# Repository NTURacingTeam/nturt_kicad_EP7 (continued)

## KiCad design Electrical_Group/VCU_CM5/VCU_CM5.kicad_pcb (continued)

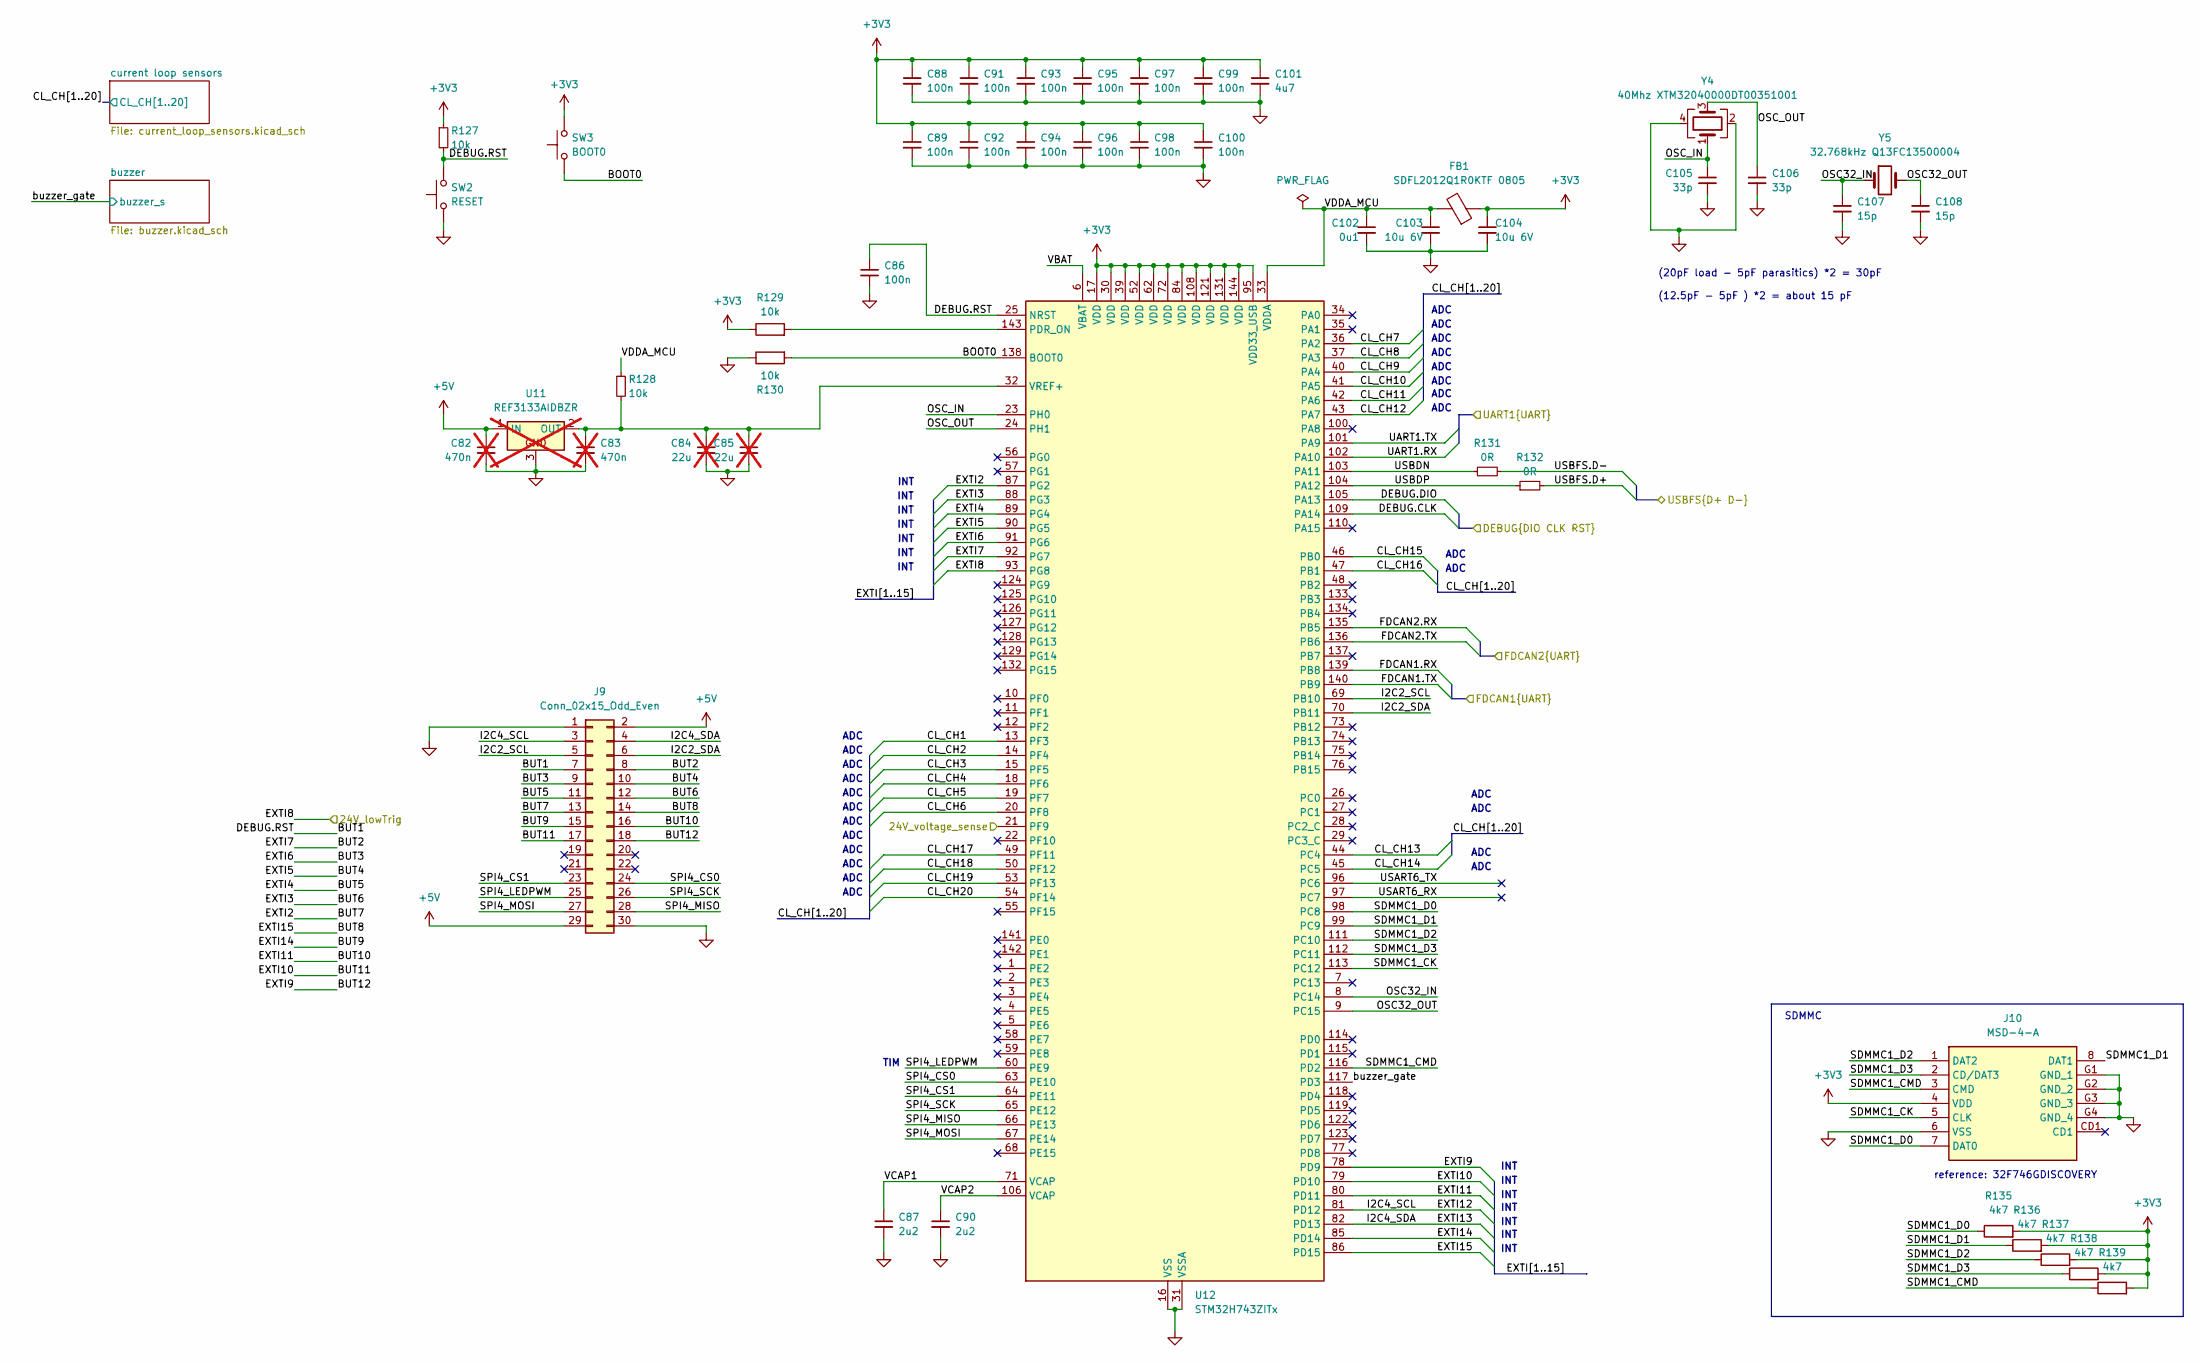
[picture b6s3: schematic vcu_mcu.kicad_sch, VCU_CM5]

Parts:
C82, C83: 470n; C_0603_1608Metric; not fitted
C84, C85: 22u; C_0805_2012Metric; not fitted
C86, C88, C89, C91, C92, C93, C94, C95, C96, C97, C98, C99, C100: 100n; C_0402_1005Metric
C87, C90: 2u2; C_0402_1005Metric
C101: 4u7; C_0402_1005Metric
C102: 0u1; C_0402_1005Metric
C103, C104: 10u 6V; C_0402_1005Metric
C105, C106: 33p; C_0402_1005Metric
C107, C108: 15p; C_0402_1005Metric
FB1: SDFL2012Q1R0KTF 0805; L_0805_2012Metric
J9: Conn_02x15_Odd_Even; PinHeader_2x15_P2.00mm_Vertical_SMD
J10: MSD-4-A; MSD4A; Mouser Part Number 179-MSD-4-A
R127, R129, R130: 10k; R_0402_1005Metric
R128: 10k; R_0603_1608Metric_Pad0.98x0.95mm_HandSolder
R131, R132: 0R; R_0402_1005Metric_Pad0.72x0.64mm_HandSolder
R135, R136, R137, R138, R139: 4k7; R_0402_1005Metric
SW2: RESET; SW_Tactile_SPST_NO_Straight_CK_PTS636Sx25SMTRLFS
SW3: BOOT0; SW_Tactile_SPST_NO_Straight_CK_PTS636Sx25SMTRLFS
U11: REF3133AIDBZR; SOT-23; not fitted
U12: STM32H743ZITx; LQFP-144_20x20mm_P0.5mm
Y4: 40Mhz XTM32040000DT00351001; Crystal_SMD_3225-4Pin_3.2x2.5mm
Y5: 32.768kHz Q13FC13500004; Crystal_SMD_3215-2Pin_3.2x1.5mm

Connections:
+3V3: C88.1, C89.1, C91.1, C92.1, C93.1, C94.1, C95.1, C96.1, C97.1, C98.1, C99.1, C100.1, C101.1, C104.1, FB1.1, J10.4 (VDD), R127.1, R129.1, R135.2, R136.2, R137.2, R138.2, R139.2, SW3.2, U12.17 (VDD), U12.30 (VDD), U12.39 (VDD), U12.52 (VDD), U12.62 (VDD), U12.72 (VDD), U12.84 (VDD), U12.95 (VDD33_USB), U12.108 (VDD), U12.121 (VDD), U12.131 (VDD), U12.144 (VDD); also elsewhere on the board
+5V: C82.1, J9.2, J9.29, U11.1 (IN); also elsewhere on the board
/DFP0.D+: R132.2; also elsewhere on the board
/DFP0.D-: R131.2; also elsewhere on the board
/STM32 CAN1/CAN.RX: U12.139 (PB8); also elsewhere on the board
/STM32 CAN1/CAN.TX: U12.140 (PB9); also elsewhere on the board
/STM32 CAN2/CAN.RX: U12.135 (PB5); also elsewhere on the board
/STM32 CAN2/CAN.TX: U12.136 (PB6); also elsewhere on the board
/power/24V_SENSE: U12.21 (PF9); also elsewhere on the board
/stlink/DEBUG.CLK: U12.109 (PA14); also elsewhere on the board
/stlink/DEBUG.DIO: U12.105 (PA13); also elsewhere on the board
/stlink/DEBUG.RST: C86.1, J9.7, R127.2, SW2.2, U12.25 (NRST); also elsewhere on the board
/stlink/VCP_MCU_UART.RX: U12.102 (PA10); also elsewhere on the board
/stlink/VCP_MCU_UART.TX: U12.101 (PA9); also elsewhere on the board
/vcu mcu/BOOT0: R130.2, SW3.1, U12.138 (BOOT0)
/vcu mcu/CL_CH1: U12.13 (PF3); also elsewhere on the board
/vcu mcu/CL_CH2: U12.14 (PF4); also elsewhere on the board
/vcu mcu/CL_CH3: U12.15 (PF5); also elsewhere on the board
/vcu mcu/CL_CH4: U12.18 (PF6); also elsewhere on the board
/vcu mcu/CL_CH5: U12.19 (PF7); also elsewhere on the board
/vcu mcu/CL_CH6: U12.20 (PF8); also elsewhere on the board
/vcu mcu/CL_CH7: U12.36 (PA2); also elsewhere on the board
/vcu mcu/CL_CH8: U12.37 (PA3); also elsewhere on the board
/vcu mcu/CL_CH9: U12.40 (PA4); also elsewhere on the board
/vcu mcu/CL_CH10: U12.41 (PA5); also elsewhere on the board
/vcu mcu/CL_CH11: U12.42 (PA6); also elsewhere on the board
/vcu mcu/CL_CH12: U12.43 (PA7); also elsewhere on the board
/vcu mcu/CL_CH13: U12.44 (PC4); also elsewhere on the board
/vcu mcu/CL_CH14: U12.45 (PC5); also elsewhere on the board
/vcu mcu/CL_CH15: U12.46 (PB0); also elsewhere on the board
/vcu mcu/CL_CH16: U12.47 (PB1); also elsewhere on the board
/vcu mcu/CL_CH17: U12.49 (PF11); also elsewhere on the board
/vcu mcu/CL_CH18: U12.50 (PF12); also elsewhere on the board
/vcu mcu/CL_CH19: U12.53 (PF13); also elsewhere on the board
/vcu mcu/CL_CH20: U12.54 (PF14); also elsewhere on the board
/vcu mcu/EXTI2: J9.13, U12.87 (PG2)
/vcu mcu/EXTI3: J9.12, U12.88 (PG3)
/vcu mcu/EXTI4: J9.11, U12.89 (PG4)
/vcu mcu/EXTI5: J9.10, U12.90 (PG5)
/vcu mcu/EXTI6: J9.9, U12.91 (PG6)
/vcu mcu/EXTI7: J9.8, U12.92 (PG7)
/vcu mcu/EXTI8: U12.93 (PG8); also elsewhere on the board
/vcu mcu/EXTI9: J9.18, U12.78 (PD9)
/vcu mcu/EXTI10: J9.17, U12.79 (PD10)
/vcu mcu/EXTI11: J9.16, U12.80 (PD11)
/vcu mcu/EXTI12: J9.3, U12.81 (PD12)
/vcu mcu/EXTI13: J9.4, U12.82 (PD13)
/vcu mcu/EXTI14: J9.15, U12.85 (PD14)
/vcu mcu/EXTI15: J9.14, U12.86 (PD15)
/vcu mcu/I2C2_SCL: J9.5, U12.69 (PB10)
/vcu mcu/I2C2_SDA: J9.6, U12.70 (PB11)
/vcu mcu/OSC32_IN: C107.1, U12.8 (PC14), Y5.1
/vcu mcu/OSC32_OUT: C108.1, U12.9 (PC15), Y5.2
/vcu mcu/OSC_IN: C105.1, U12.23 (PH0), Y4.1
/vcu mcu/OSC_OUT: C106.1, U12.24 (PH1), Y4.3
/vcu mcu/SDMMC1_CK: J10.5 (CLK), U12.113 (PC12)
/vcu mcu/SDMMC1_CMD: J10.3 (CMD), R139.1, U12.116 (PD2)
/vcu mcu/SDMMC1_D0: J10.7 (DAT0), R135.1, U12.98 (PC8)
/vcu mcu/SDMMC1_D1: J10.8 (DAT1), R136.1, U12.99 (PC9)
/vcu mcu/SDMMC1_D2: J10.1 (DAT2), R137.1, U12.111 (PC10)
/vcu mcu/SDMMC1_D3: J10.2 (CD/DAT3), R138.1, U12.112 (PC11)
/vcu mcu/SPI4_CS0: J9.24, U12.63 (PE10)
/vcu mcu/SPI4_CS1: J9.23, U12.64 (PE11)
/vcu mcu/SPI4_LEDPWM: J9.25, U12.60 (PE9)
/vcu mcu/SPI4_MISO: J9.28, U12.66 (PE13)
/vcu mcu/SPI4_MOSI: J9.27, U12.67 (PE14)
/vcu mcu/SPI4_SCK: J9.26, U12.65 (PE12)
/vcu mcu/USART6_RX: U12.97 (PC7)
/vcu mcu/USART6_TX: U12.96 (PC6)
/vcu mcu/USBDN: R131.1, U12.103 (PA11)
/vcu mcu/USBDP: R132.1, U12.104 (PA12)
/vcu mcu/VBAT: U12.6 (VBAT)
/vcu mcu/VCAP1: C87.1, U12.71 (VCAP)
/vcu mcu/VCAP2: C90.1, U12.106 (VCAP)
/vcu mcu/VDDA_MCU: C102.1, C103.1, FB1.2, R128.1, U12.33 (VDDA)
/vcu mcu/buzzer_gate: U12.117 (PD3); also elsewhere on the board
GND: C82.2, C83.2, C84.2, C85.2, C86.2, C87.2, C88.2, C89.2, C90.2, C91.2, C92.2, C93.2, C94.2, C95.2, C96.2, C97.2, C98.2, C99.2, C100.2, C101.2, C102.2, C103.2, C104.2, C105.2, C106.2, C107.2, C108.2, J9.1, J9.30, J10.6 (VSS), J10.G1 (GND_1), J10.G2 (GND_2), J10.G3 (GND_3), J10.G4 (GND_4), R130.1, SW2.1, U11.3, U12.16 (VSS), U12.31 (VSSA), U12.38 (VSS), U12.51 (VSS), U12.61 (VSS), U12.83 (VSS), U12.94 (VSS), U12.107 (VSS), U12.120 (VSS), U12.130 (VSS), Y4.2, Y4.4; also elsewhere on the board
unnamed: C83.1, C84.1, C85.1, R128.2, U11.2 (OUT), U12.32 (VREF+)
unnamed: R129.2, U12.143 (PDR_ON)

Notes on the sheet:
ADC
SDMMC
INT
(20pF load - 5pF parasitics) *2 = 30pF (12.5pF - 5pF ) *2 = about 15 pF
reference: 32F746GDISCOVERY
TIM

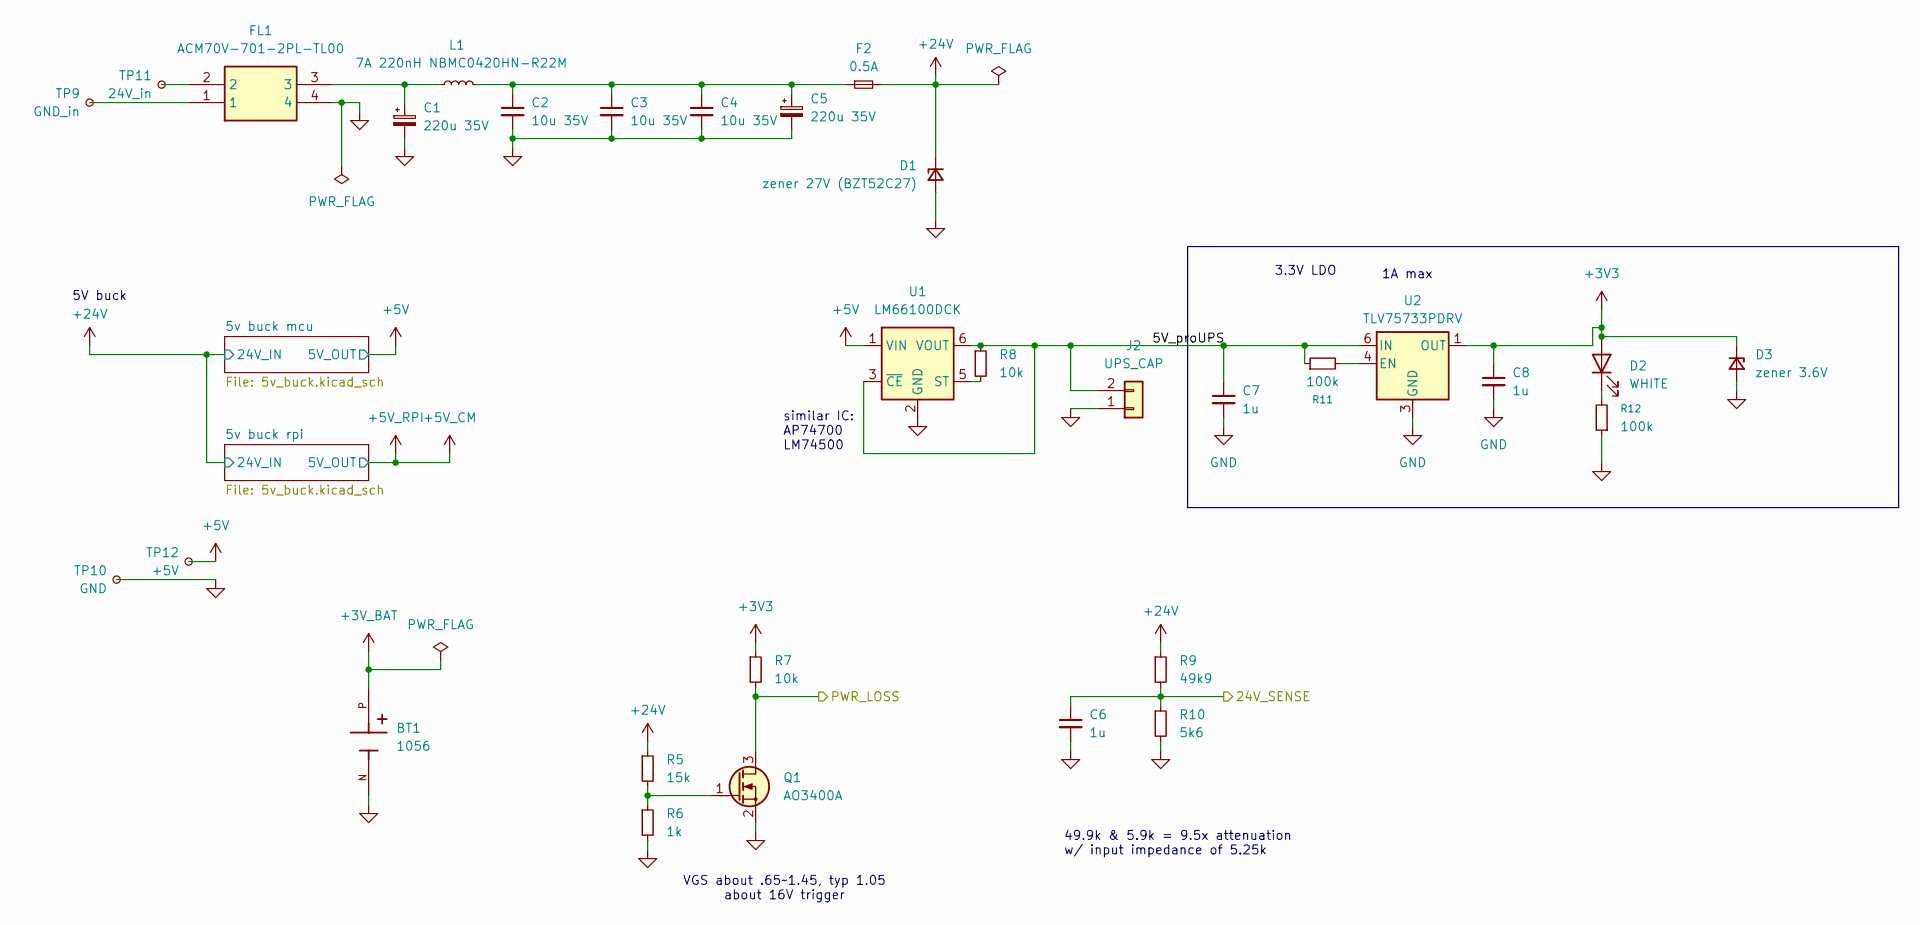
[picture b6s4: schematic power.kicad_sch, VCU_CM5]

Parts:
BT1: 1056; BAT_1056; PARTREV D
C1, C5: 220u 35V; CP_Elec_6.3x5.2
C2, C3, C4: 10u 35V; C_1206_3216Metric
C6, C7, C8: 1u; C_0402_1005Metric
D1: zener 27V (BZT52C27); D_SOD-123
D2: WHITE; LED_0603_1608Metric
D3: zener 3.6V; D_SOD-123
F2: 0.5A; Fuse_1206_3216Metric
FL1: ACM70V-701-2PL-TL00; Common_Mode_Choke_4A_ACM70V7012PLTL00; Mouser Part Number 810-ACM70V7012PLTL00
J2: UPS_CAP; PinHeader_1x02_P2.00mm_Horizontal
L1: 7A 220nH NBMC0420HN-R22M; L_Ferrocore_DLG-0403
Q1: AO3400A; SOT-23
R5: 15k; R_0402_1005Metric
R6: 1k; R_0402_1005Metric
R7, R8: 10k; R_0402_1005Metric
R9: 49k9; R_0402_1005Metric
R10: 5k6; R_0402_1005Metric
R11, R12: 100k; R_0402_1005Metric
TP9: GND_in; edge_pad_1.4mm_0.7mm
TP10: GND; edge_pad_1.4mm_0.7mm
TP11: 24V_in; edge_pad_1.4mm_0.7mm
TP12: +5V; edge_pad_1.4mm_0.7mm
U1: LM66100DCK; SOT-363_SC-70-6
U2: TLV75733PDRV; WSON-6-1EP_2x2mm_P0.65mm_EP1x1.6mm

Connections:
+3V3: C8.1, D2.2 (A), D3.1 (K), R7.1, U2.1 (OUT); also elsewhere on the board
+3V_BAT: BT1.P; also elsewhere on the board
+5V: TP12.1, U1.1 (VIN); also elsewhere on the board
+24V: D1.1 (K), F2.2, R5.1, R9.1; also elsewhere on the board
/power/5V_proUPS: C7.1, J2.2, R8.1, R11.1, U1.3 (~CE), U1.6 (VOUT), U2.6 (IN)
/power/24V_SENSE: C6.1, R9.2, R10.1; also elsewhere on the board
/vcu mcu/EXTI8: Q1.3 (D), R7.2; also elsewhere on the board
GND: BT1.N, C1.2, C2.2, C3.2, C4.2, C5.2, C6.2, C7.2, C8.2, D1.2 (A), D3.2 (A), FL1.4, J2.1, Q1.2 (S), R6.2, R10.2, R12.1, TP10.1, U1.2 (GND), U2.3 (GND), U2.7 (GND); also elsewhere on the board
unnamed: C1.1, FL1.3, L1.1
unnamed: C2.1, C3.1, C4.1, C5.1, F2.1, L1.2
unnamed: D2.1 (K), R12.2
unnamed: FL1.1, TP9.1
unnamed: FL1.2, TP11.1
unnamed: Q1.1 (G), R5.2, R6.1
unnamed: R8.2, U1.5 (ST)
unnamed: R11.2, U2.4 (EN)

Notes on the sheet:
similar IC: AP74700 LM74500
5V buck
49.9k & 5.9k = 9.5x attenuation w/ input impedance of 5.25k
1A max
VGS about .65~1.45, typ 1.05 about 16V trigger
3.3V LDO

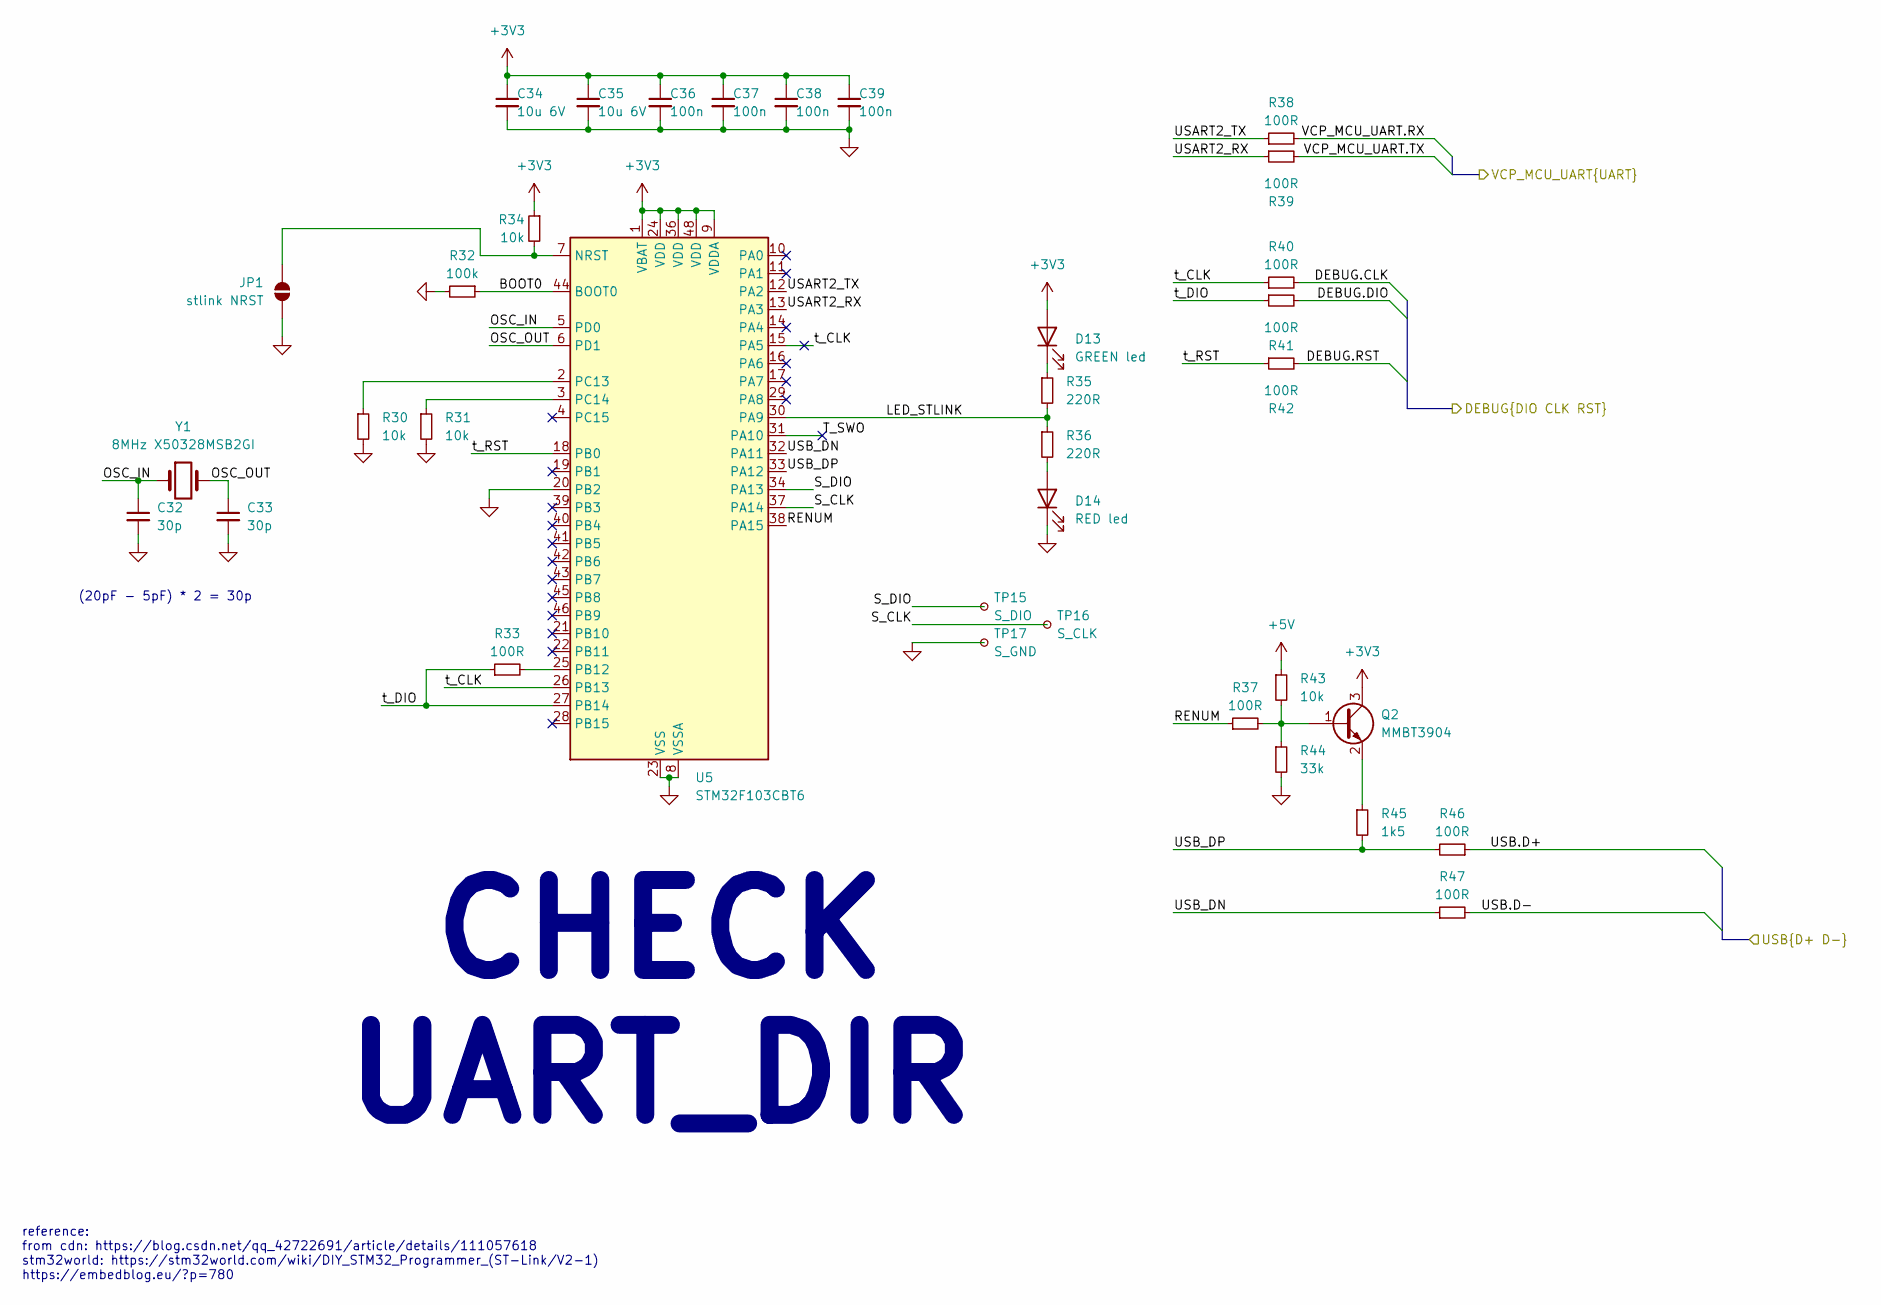
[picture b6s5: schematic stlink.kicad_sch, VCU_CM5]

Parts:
C32, C33: 30p; C_0402_1005Metric
C34, C35: 10u 6V; C_0402_1005Metric
C36, C37, C38, C39: 100n; C_0402_1005Metric
D13: GREEN led; LED_0603_1608Metric
D14: RED led; LED_0603_1608Metric
JP1: stlink NRST; SolderJumper-2_P1.3mm_Open_RoundedPad1.0x1.5mm
Q2: MMBT3904; SOT-23
R30, R31, R34, R43: 10k; R_0402_1005Metric
R32: 100k; R_0402_1005Metric
R33, R37: 100R; R_0402_1005Metric
R35, R36: 220R; R_0402_1005Metric
R38, R39, R40, R41, R42: 100R; R_0603_1608Metric_Pad0.98x0.95mm_HandSolder
R44: 33k; R_0402_1005Metric
R45: 1k5; R_0402_1005Metric
R46, R47: 100R; R_0402_1005Metric_Pad0.72x0.64mm_HandSolder
TP15: S_DIO; TestPoint_Pad_D1.0mm
TP16: S_CLK; TestPoint_Pad_D1.0mm
TP17: S_GND; TestPoint_Pad_D1.0mm
U5: STM32F103CBT6; LQFP-48_7x7mm_P0.5mm
Y1: 8MHz X50328MSB2GI; Crystal_SMD_5032-2Pin_5.0x3.2mm

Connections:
+3V3: C34.1, C35.1, C36.1, C37.1, C38.1, C39.1, D13.2 (A), Q2.3 (C), R34.1, U5.1 (VBAT), U5.9 (VDDA), U5.24 (VDD), U5.36 (VDD), U5.48 (VDD); also elsewhere on the board
+5V: R43.1; also elsewhere on the board
/DFP3.D+: R46.1; also elsewhere on the board
/DFP3.D-: R47.2; also elsewhere on the board
/stlink/BOOT0: R32.1, U5.44 (BOOT0)
/stlink/DEBUG.CLK: R40.2; also elsewhere on the board
/stlink/DEBUG.DIO: R41.2; also elsewhere on the board
/stlink/DEBUG.RST: R42.2; also elsewhere on the board
/stlink/LED_STLINK: R35.2, R36.1, U5.30 (PA9)
/stlink/OSC_IN: C32.1, U5.5 (PD0), Y1.1
/stlink/OSC_OUT: C33.1, U5.6 (PD1), Y1.2
/stlink/RENUM: R37.1, U5.38 (PA15)
/stlink/S_CLK: TP16.1, U5.37 (PA14)
/stlink/S_DIO: TP15.1, U5.34 (PA13)
/stlink/T_SWO: U5.31 (PA10)
/stlink/USART2_RX: R39.1, U5.13 (PA3)
/stlink/USART2_TX: R38.1, U5.12 (PA2)
/stlink/USB_DN: R47.1, U5.32 (PA11)
/stlink/USB_DP: R45.2, R46.2, U5.33 (PA12)
/stlink/VCP_MCU_UART.RX: R38.2; also elsewhere on the board
/stlink/VCP_MCU_UART.TX: R39.2; also elsewhere on the board
/stlink/t_CLK: R40.1, U5.15 (PA5), U5.26 (PB13)
/stlink/t_DIO: R33.1, R41.1, U5.27 (PB14)
/stlink/t_RST: R42.1, U5.18 (PB0)
GND: C32.2, C33.2, C34.2, C35.2, C36.2, C37.2, C38.2, C39.2, D14.1 (K), JP1.2 (B), R30.2, R31.2, R32.2, R44.2, TP17.1, U5.8 (VSSA), U5.20 (PB2), U5.23 (VSS), U5.35 (VSS), U5.47 (VSS); also elsewhere on the board
unnamed: D13.1 (K), R35.1
unnamed: D14.2 (A), R36.2
unnamed: JP1.1 (A), R34.2, U5.7 (NRST)
unnamed: Q2.1 (B), R37.2, R43.2, R44.1
unnamed: Q2.2 (E), R45.1
unnamed: R33.2, U5.25 (PB12)
unnamed: R30.1, U5.2 (PC13)
unnamed: R31.1, U5.3 (PC14)

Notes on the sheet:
(20pF - 5pF) * 2 = 30p
reference: from cdn: https://blog.csdn.net/qq_42722691/article/details/111057618 stm32world: https://stm32world.com/wiki/DIY_STM32_Programmer_(ST-Link/V2-1) https://embedblog.eu/?p=780
CHECK UART_DIR

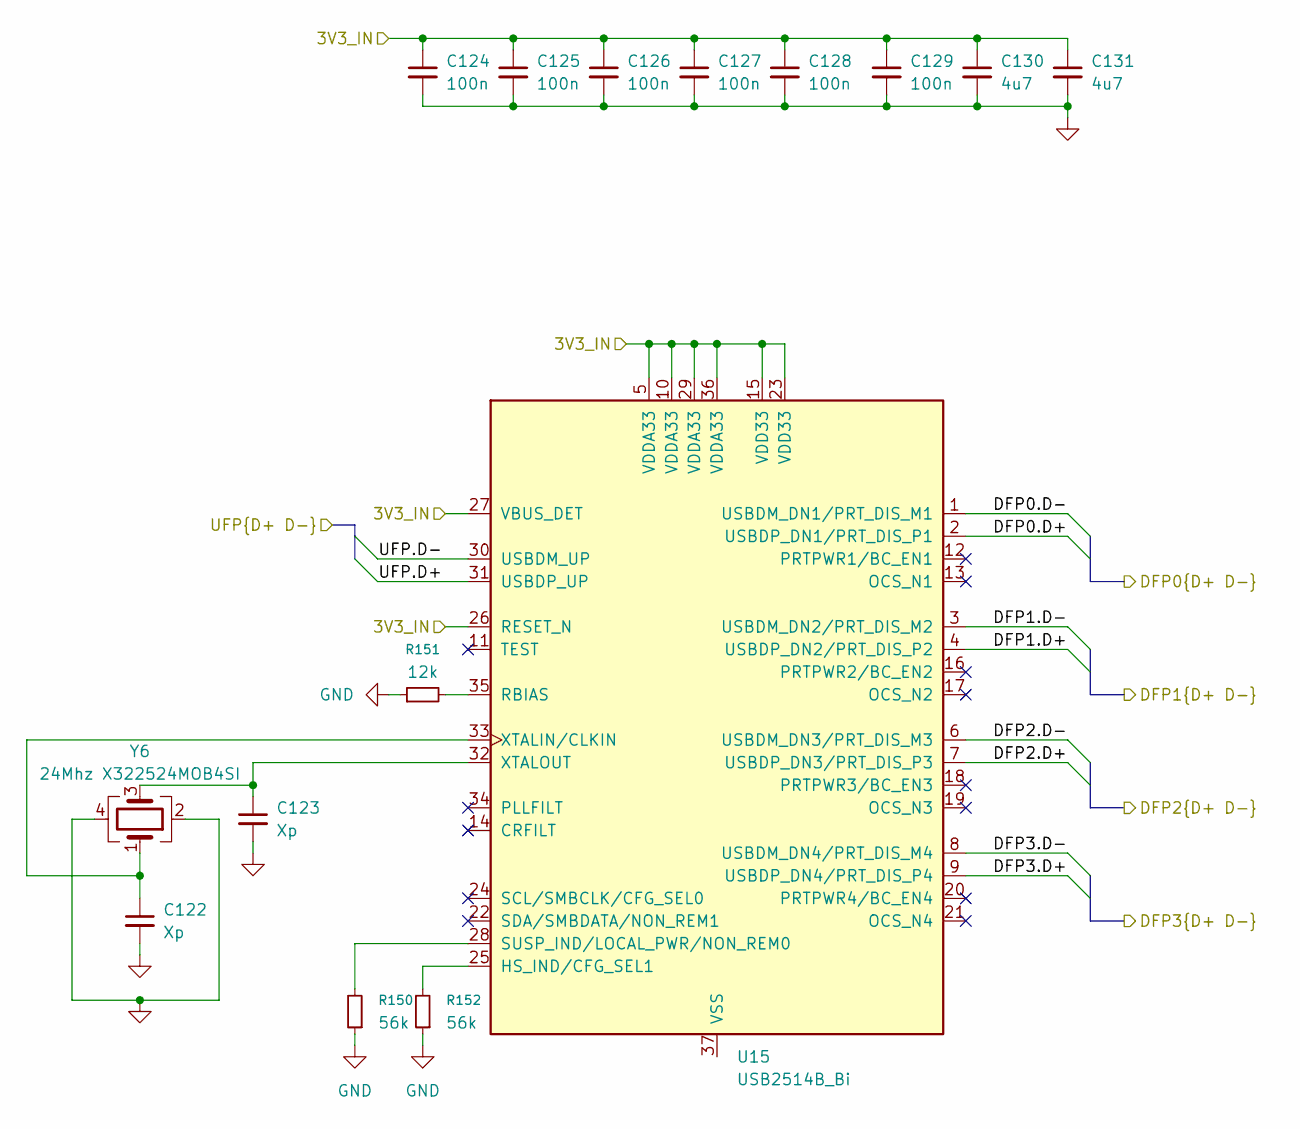
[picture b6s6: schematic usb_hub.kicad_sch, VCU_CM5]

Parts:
C122, C123: Xp; C_0402_1005Metric
C124, C125, C126, C127, C128, C129: 100n; C_0402_1005Metric
C130, C131: 4u7; C_0402_1005Metric
R150, R152: 56k; R_0402_1005Metric
R151: 12k; R_0402_1005Metric
U15: USB2514B_Bi; QFN-36-1EP_6x6mm_P0.5mm_EP3.7x3.7mm
Y6: 24Mhz X322524MOB4SI; Crystal_SMD_3225-4Pin_3.2x2.5mm

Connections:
+3V3_CMOUT: C124.1, C125.1, C126.1, C127.1, C128.1, C129.1, C130.1, C131.1, U15.5 (VDDA33), U15.10 (VDDA33), U15.15 (VDD33), U15.23 (VDD33), U15.26 (RESET_N), U15.27 (VBUS_DET), U15.29 (VDDA33), U15.36 (VDDA33); also elsewhere on the board
/DFP0.D+: U15.2 (USBDP_DN1/PRT_DIS_P1); also elsewhere on the board
/DFP0.D-: U15.1 (USBDM_DN1/PRT_DIS_M1); also elsewhere on the board
/DFP1.D+: U15.4 (USBDP_DN2/PRT_DIS_P2)
/DFP1.D-: U15.3 (USBDM_DN2/PRT_DIS_M2)
/DFP2.D+: U15.7 (USBDP_DN3/PRT_DIS_P3)
/DFP2.D-: U15.6 (USBDM_DN3/PRT_DIS_M3)
/DFP3.D+: U15.9 (USBDP_DN4/PRT_DIS_P4); also elsewhere on the board
/DFP3.D-: U15.8 (USBDM_DN4/PRT_DIS_M4); also elsewhere on the board
/computer/USB3_0.D+: U15.31 (USBDP_UP); also elsewhere on the board
/computer/USB3_0.D-: U15.30 (USBDM_UP); also elsewhere on the board
GND: C122.2, C123.2, C124.2, C125.2, C126.2, C127.2, C128.2, C129.2, C130.2, C131.2, R150.1, R151.1, R152.1, Y6.2, Y6.4; also elsewhere on the board
unnamed: R152.2, U15.25 (HS_IND/CFG_SEL1)
unnamed: R151.2, U15.35 (RBIAS)
unnamed: R150.2, U15.28 (SUSP_IND/LOCAL_PWR/NON_REM0)
unnamed: C122.1, U15.33 (XTALIN/CLKIN), Y6.1
unnamed: C123.1, U15.32 (XTALOUT), Y6.3
